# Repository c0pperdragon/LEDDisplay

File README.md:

# LEDDisplay

To go with all my lumacode digitizer boards, we also need something to 
display the output in a proper retro fashion. So a big LED matrix display that can accept
lumacode natively would be just the right thing for that.

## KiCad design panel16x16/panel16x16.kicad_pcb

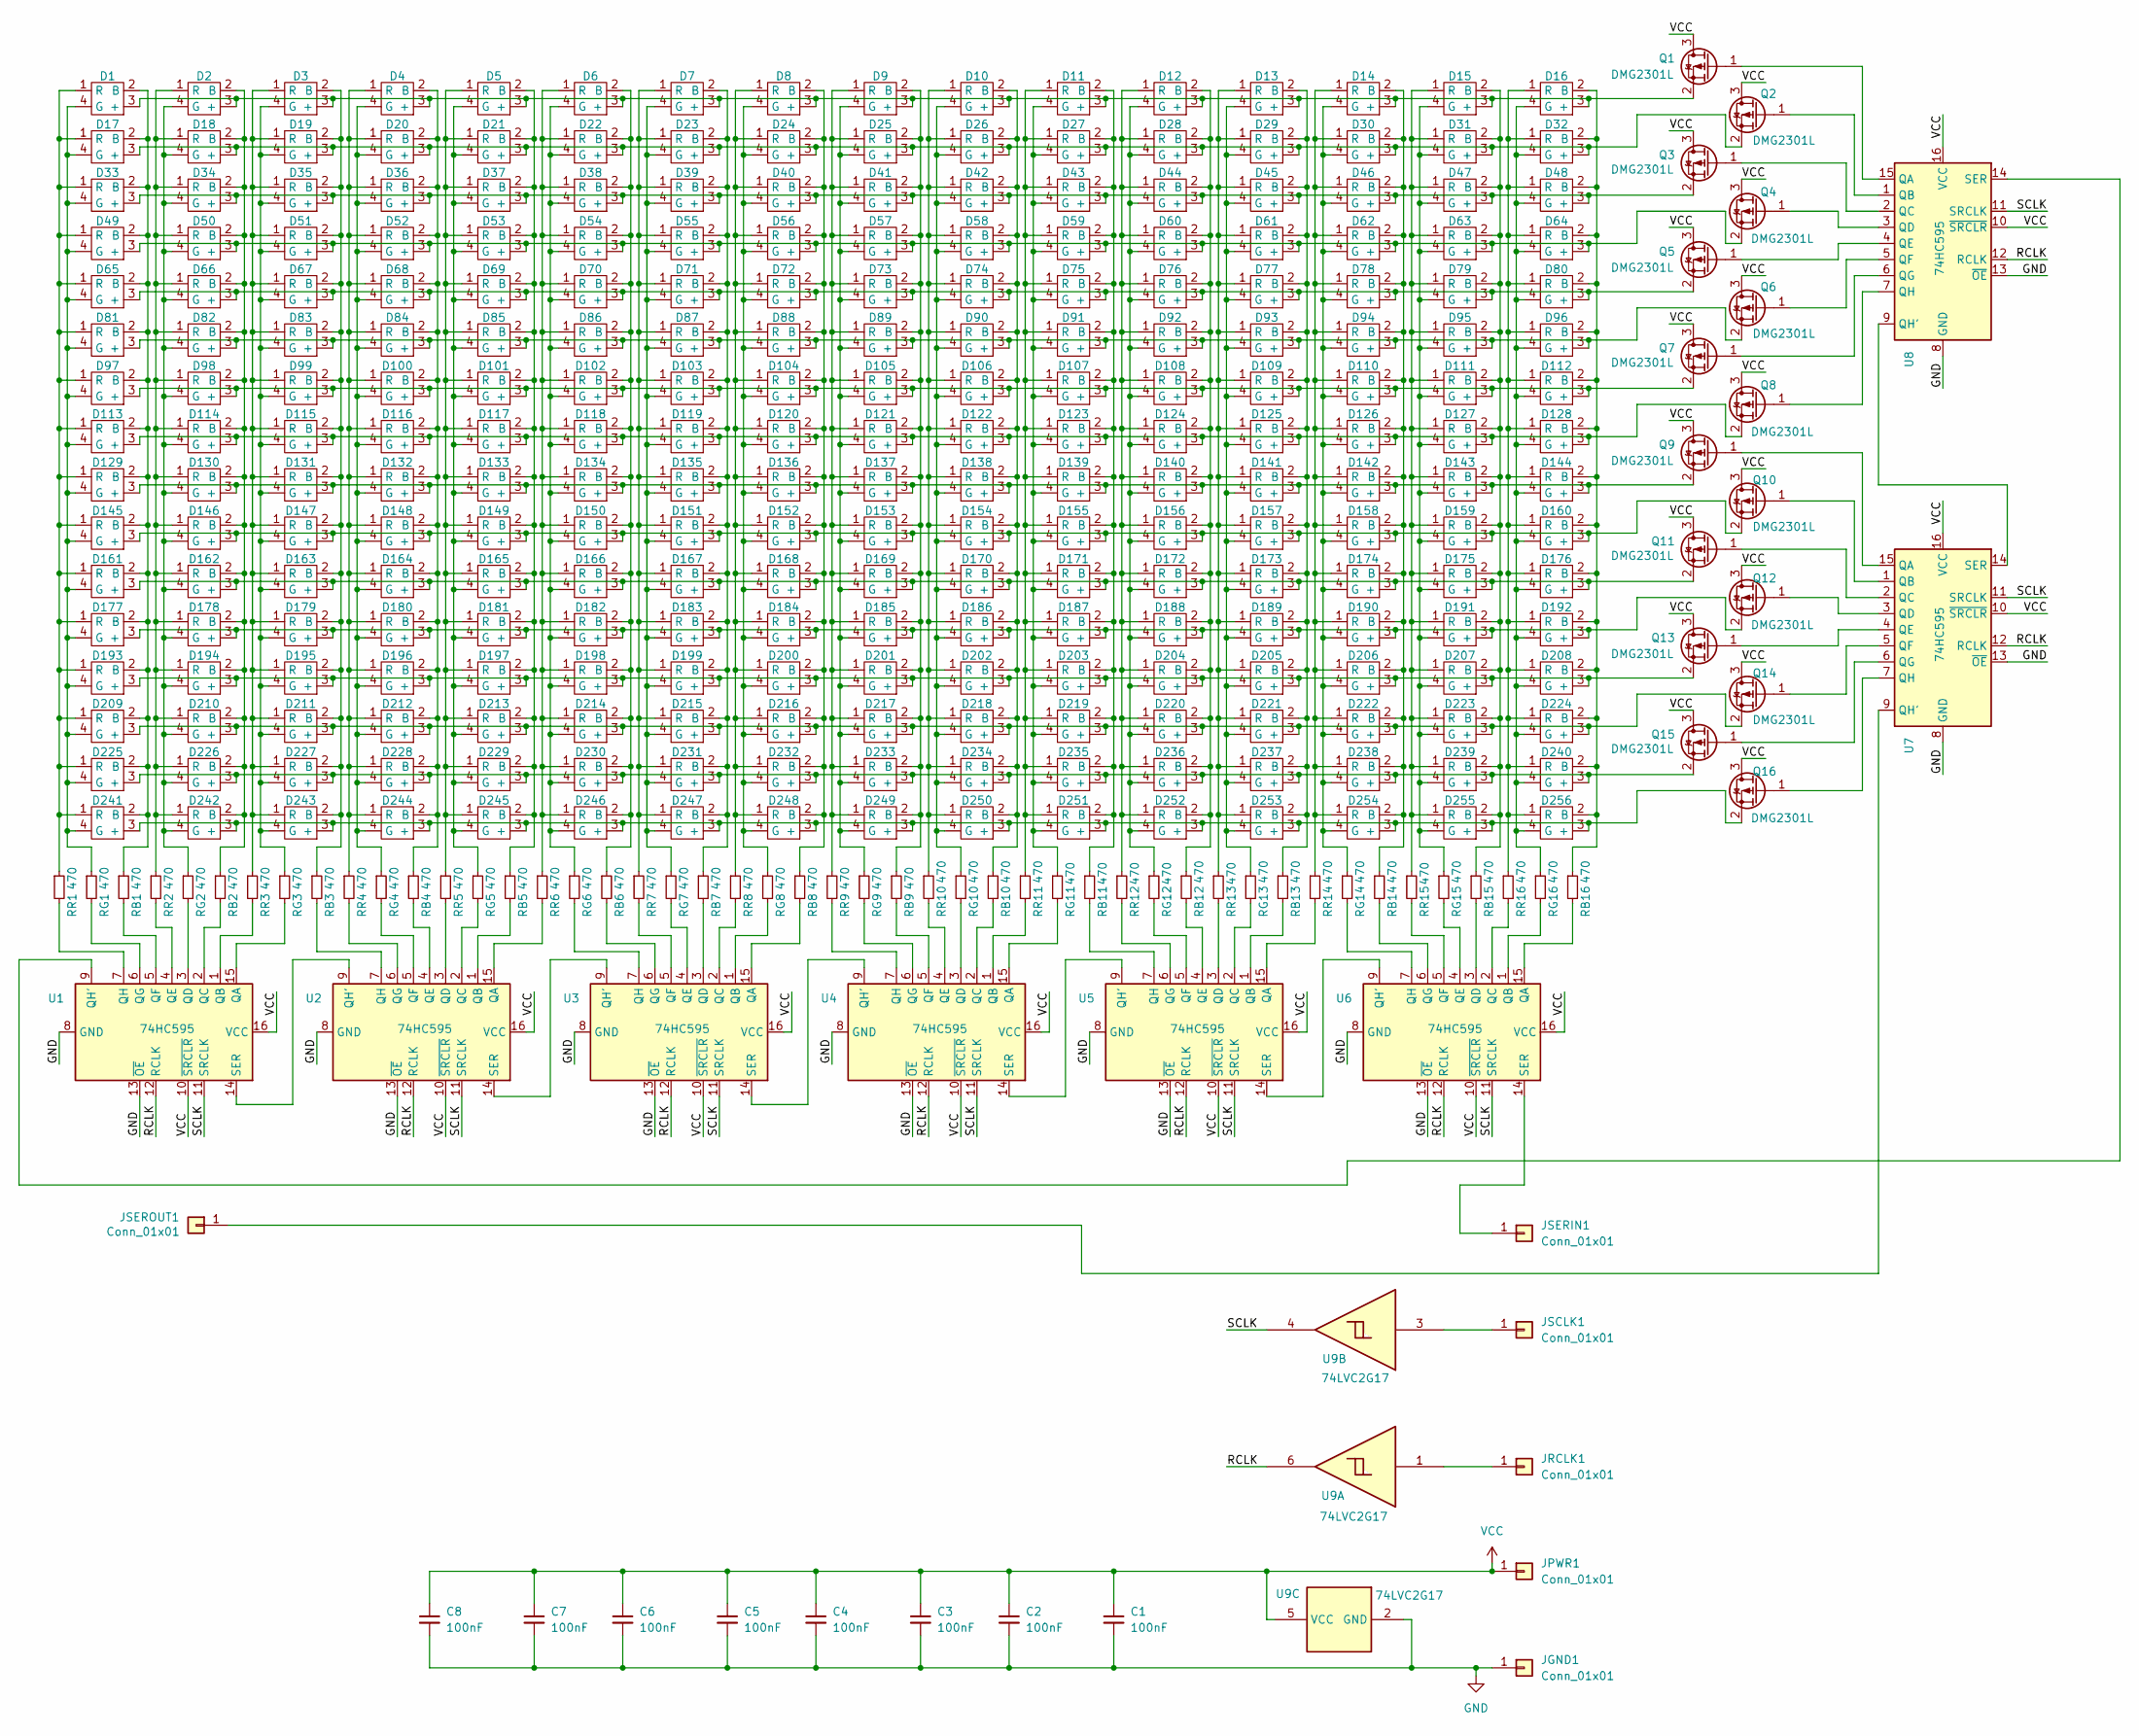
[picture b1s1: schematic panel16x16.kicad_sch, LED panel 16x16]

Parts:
C1, C2, C3, C4, C5, C6, C7, C8: 100nF; C_0603_1608Metric
D1, D2, D3, D4, D5, D6, D7, D8, D9, D10, D11, D12, D13, D14, D15, D16, D17, D18, D19, D20, D21, D22, D23, D24, D25, D26, D27, D28, D29, D30, D31, D32, D33, D34, D35, D36, D37, D38, D39, D40, D41, D42, D43, D44, D45, D46, D47, D48, D49, D50, D51, D52, D53, D54, D55, D56, D57, D58, D59, D60, D61, D62, D63, D64, D65, D66, D67, D68, D69, D70, D71, D72, D73, D74, D75, D76, D77, D78, D79, D80, D81, D82, D83, D84, D85, D86, D87, D88, D89, D90, D91, D92, D93, D94, D95, D96, D97, D98, D99, D100, D101, D102, D103, D104, D105, D106, D107, D108, D109, D110, D111, D112, D113, D114, D115, D116, D117, D118, D119, D120, D121, D122, D123, D124, D125, D126, D127, D128, D129, D130, D131, D132, D133, D134, D135, D136, D137, D138, D139, D140, D141, D142, D143, D144, D145, D146, D147, D148, D149, D150, D151, D152, D153, D154, D155, D156, D157, D158, D159, D160, D161, D162, D163, D164, D165, D166, D167, D168, D169, D170, D171, D172, D173, D174, D175, D176, D177, D178, D179, D180, D181, D182, D183, D184, D185, D186, D187, D188, D189, D190, D191, D192, D193, D194, D195, D196, D197, D198, D199, D200, D201, D202, D203, D204, D205, D206, D207, D208, D209, D210, D211, D212, D213, D214, D215, D216, D217, D218, D219, D220, D221, D222, D223, D224, D225, D226, D227, D228, D229, D230, D231, D232, D233, D234, D235, D236, D237, D238, D239, D240, D241, D242, D243, D244, D245, D246, D247, D248, D249, D250, D251, D252, D253, D254, D255, D256: B2020-RGBA
JGND1: Conn_01x01; TestPoint_Pad_2.0x2.0mm
JPWR1: Conn_01x01; TestPoint_Pad_2.0x2.0mm
JRCLK1: Conn_01x01; TestPoint_Pad_2.0x2.0mm
JSCLK1: Conn_01x01; TestPoint_Pad_2.0x2.0mm
JSERIN1: Conn_01x01; TestPoint_Pad_2.0x2.0mm
JSEROUT1: Conn_01x01; TestPoint_Pad_2.0x2.0mm
Q1, Q2, Q3, Q4, Q5, Q6, Q7, Q8, Q9, Q10, Q11, Q12, Q13, Q14, Q15, Q16: DMG2301L; SOT-23
RB1, RB2, RB3, RB4, RB5, RB6, RB7, RB8, RB9, RB10, RB11, RB12, RB13, RB14, RB15, RB16: 470; R_0603_1608Metric
RG1, RG2, RG3, RG4, RG5, RG6, RG7, RG8, RG9, RG10, RG11, RG12, RG13, RG14, RG15, RG16: 470; R_0603_1608Metric
RR1, RR2, RR3, RR4, RR5, RR6, RR7, RR8, RR9, RR10, RR11, RR12, RR13, RR14, RR15, RR16: 470; R_0603_1608Metric
U1, U2, U3, U4, U5, U6, U7, U8: 74HC595; TSSOP-16_4.4x5mm_P0.65mm
U9: 74LVC2G17; SOT-23-6

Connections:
/RCLK: U1.12 (RCLK), U2.12 (RCLK), U3.12 (RCLK), U4.12 (RCLK), U5.12 (RCLK), U6.12 (RCLK), U7.12 (RCLK), U8.12 (RCLK), U9.6
/SCLK: U1.11 (SRCLK), U2.11 (SRCLK), U3.11 (SRCLK), U4.11 (SRCLK), U5.11 (SRCLK), U6.11 (SRCLK), U7.11 (SRCLK), U8.11 (SRCLK), U9.4
GND: C1.2, C2.2, C3.2, C4.2, C5.2, C6.2, C7.2, C8.2, JGND1.1, U1.8 (GND), U1.13 (~OE), U2.8 (GND), U2.13 (~OE), U3.8 (GND), U3.13 (~OE), U4.8 (GND), U4.13 (~OE), U5.8 (GND), U5.13 (~OE), U6.8 (GND), U6.13 (~OE), U7.8 (GND), U7.13 (~OE), U8.8 (GND), U8.13 (~OE), U9.2 (GND)
unnamed: D1.3 (+), D2.3 (+), D3.3 (+), D4.3 (+), D5.3 (+), D6.3 (+), D7.3 (+), D8.3 (+), D9.3 (+), D10.3 (+), D11.3 (+), D12.3 (+), D13.3 (+), D14.3 (+), D15.3 (+), D16.3 (+), Q1.2 (S)
unnamed: D1.2 (B), D17.2 (B), D33.2 (B), D49.2 (B), D65.2 (B), D81.2 (B), D97.2 (B), D113.2 (B), D129.2 (B), D145.2 (B), D161.2 (B), D177.2 (B), D193.2 (B), D209.2 (B), D225.2 (B), D241.2 (B), RB1.1
unnamed: D1.4 (G), D17.4 (G), D33.4 (G), D49.4 (G), D65.4 (G), D81.4 (G), D97.4 (G), D113.4 (G), D129.4 (G), D145.4 (G), D161.4 (G), D177.4 (G), D193.4 (G), D209.4 (G), D225.4 (G), D241.4 (G), RG1.1
unnamed: D1.1 (R), D17.1 (R), D33.1 (R), D49.1 (R), D65.1 (R), D81.1 (R), D97.1 (R), D113.1 (R), D129.1 (R), D145.1 (R), D161.1 (R), D177.1 (R), D193.1 (R), D209.1 (R), D225.1 (R), D241.1 (R), RR1.1
unnamed: D10.2 (B), D26.2 (B), D42.2 (B), D58.2 (B), D74.2 (B), D90.2 (B), D106.2 (B), D122.2 (B), D138.2 (B), D154.2 (B), D170.2 (B), D186.2 (B), D202.2 (B), D218.2 (B), D234.2 (B), D250.2 (B), RB10.1
unnamed: D10.4 (G), D26.4 (G), D42.4 (G), D58.4 (G), D74.4 (G), D90.4 (G), D106.4 (G), D122.4 (G), D138.4 (G), D154.4 (G), D170.4 (G), D186.4 (G), D202.4 (G), D218.4 (G), D234.4 (G), D250.4 (G), RG10.1
unnamed: D10.1 (R), D26.1 (R), D42.1 (R), D58.1 (R), D74.1 (R), D90.1 (R), D106.1 (R), D122.1 (R), D138.1 (R), D154.1 (R), D170.1 (R), D186.1 (R), D202.1 (R), D218.1 (R), D234.1 (R), D250.1 (R), RR10.1
unnamed: D17.3 (+), D18.3 (+), D19.3 (+), D20.3 (+), D21.3 (+), D22.3 (+), D23.3 (+), D24.3 (+), D25.3 (+), D26.3 (+), D27.3 (+), D28.3 (+), D29.3 (+), D30.3 (+), D31.3 (+), D32.3 (+), Q2.2 (S)
unnamed: D33.3 (+), D34.3 (+), D35.3 (+), D36.3 (+), D37.3 (+), D38.3 (+), D39.3 (+), D40.3 (+), D41.3 (+), D42.3 (+), D43.3 (+), D44.3 (+), D45.3 (+), D46.3 (+), D47.3 (+), D48.3 (+), Q3.2 (S)
unnamed: D49.3 (+), D50.3 (+), D51.3 (+), D52.3 (+), D53.3 (+), D54.3 (+), D55.3 (+), D56.3 (+), D57.3 (+), D58.3 (+), D59.3 (+), D60.3 (+), D61.3 (+), D62.3 (+), D63.3 (+), D64.3 (+), Q4.2 (S)
unnamed: D65.3 (+), D66.3 (+), D67.3 (+), D68.3 (+), D69.3 (+), D70.3 (+), D71.3 (+), D72.3 (+), D73.3 (+), D74.3 (+), D75.3 (+), D76.3 (+), D77.3 (+), D78.3 (+), D79.3 (+), D80.3 (+), Q5.2 (S)
unnamed: D81.3 (+), D82.3 (+), D83.3 (+), D84.3 (+), D85.3 (+), D86.3 (+), D87.3 (+), D88.3 (+), D89.3 (+), D90.3 (+), D91.3 (+), D92.3 (+), D93.3 (+), D94.3 (+), D95.3 (+), D96.3 (+), Q6.2 (S)
unnamed: D97.3 (+), D98.3 (+), D99.3 (+), D100.3 (+), D101.3 (+), D102.3 (+), D103.3 (+), D104.3 (+), D105.3 (+), D106.3 (+), D107.3 (+), D108.3 (+), D109.3 (+), D110.3 (+), D111.3 (+), D112.3 (+), Q7.2 (S)
unnamed: D4.2 (B), D20.2 (B), D36.2 (B), D52.2 (B), D68.2 (B), D84.2 (B), D100.2 (B), D116.2 (B), D132.2 (B), D148.2 (B), D164.2 (B), D180.2 (B), D196.2 (B), D212.2 (B), D228.2 (B), D244.2 (B), RB4.1
unnamed: D4.4 (G), D20.4 (G), D36.4 (G), D52.4 (G), D68.4 (G), D84.4 (G), D100.4 (G), D116.4 (G), D132.4 (G), D148.4 (G), D164.4 (G), D180.4 (G), D196.4 (G), D212.4 (G), D228.4 (G), D244.4 (G), RG4.1
unnamed: D4.1 (R), D20.1 (R), D36.1 (R), D52.1 (R), D68.1 (R), D84.1 (R), D100.1 (R), D116.1 (R), D132.1 (R), D148.1 (R), D164.1 (R), D180.1 (R), D196.1 (R), D212.1 (R), D228.1 (R), D244.1 (R), RR4.1
unnamed: D5.2 (B), D21.2 (B), D37.2 (B), D53.2 (B), D69.2 (B), D85.2 (B), D101.2 (B), D117.2 (B), D133.2 (B), D149.2 (B), D165.2 (B), D181.2 (B), D197.2 (B), D213.2 (B), D229.2 (B), D245.2 (B), RB5.1
unnamed: D5.4 (G), D21.4 (G), D37.4 (G), D53.4 (G), D69.4 (G), D85.4 (G), D101.4 (G), D117.4 (G), D133.4 (G), D149.4 (G), D165.4 (G), D181.4 (G), D197.4 (G), D213.4 (G), D229.4 (G), D245.4 (G), RG5.1
unnamed: D5.1 (R), D21.1 (R), D37.1 (R), D53.1 (R), D69.1 (R), D85.1 (R), D101.1 (R), D117.1 (R), D133.1 (R), D149.1 (R), D165.1 (R), D181.1 (R), D197.1 (R), D213.1 (R), D229.1 (R), D245.1 (R), RR5.1
unnamed: D6.2 (B), D22.2 (B), D38.2 (B), D54.2 (B), D70.2 (B), D86.2 (B), D102.2 (B), D118.2 (B), D134.2 (B), D150.2 (B), D166.2 (B), D182.2 (B), D198.2 (B), D214.2 (B), D230.2 (B), D246.2 (B), RB6.1
unnamed: D6.4 (G), D22.4 (G), D38.4 (G), D54.4 (G), D70.4 (G), D86.4 (G), D102.4 (G), D118.4 (G), D134.4 (G), D150.4 (G), D166.4 (G), D182.4 (G), D198.4 (G), D214.4 (G), D230.4 (G), D246.4 (G), RG6.1
unnamed: D6.1 (R), D22.1 (R), D38.1 (R), D54.1 (R), D70.1 (R), D86.1 (R), D102.1 (R), D118.1 (R), D134.1 (R), D150.1 (R), D166.1 (R), D182.1 (R), D198.1 (R), D214.1 (R), D230.1 (R), D246.1 (R), RR6.1
unnamed: D7.2 (B), D23.2 (B), D39.2 (B), D55.2 (B), D71.2 (B), D87.2 (B), D103.2 (B), D119.2 (B), D135.2 (B), D151.2 (B), D167.2 (B), D183.2 (B), D199.2 (B), D215.2 (B), D231.2 (B), D247.2 (B), RB7.1
unnamed: D7.4 (G), D23.4 (G), D39.4 (G), D55.4 (G), D71.4 (G), D87.4 (G), D103.4 (G), D119.4 (G), D135.4 (G), D151.4 (G), D167.4 (G), D183.4 (G), D199.4 (G), D215.4 (G), D231.4 (G), D247.4 (G), RG7.1
unnamed: D7.1 (R), D23.1 (R), D39.1 (R), D55.1 (R), D71.1 (R), D87.1 (R), D103.1 (R), D119.1 (R), D135.1 (R), D151.1 (R), D167.1 (R), D183.1 (R), D199.1 (R), D215.1 (R), D231.1 (R), D247.1 (R), RR7.1
unnamed: D8.2 (B), D24.2 (B), D40.2 (B), D56.2 (B), D72.2 (B), D88.2 (B), D104.2 (B), D120.2 (B), D136.2 (B), D152.2 (B), D168.2 (B), D184.2 (B), D200.2 (B), D216.2 (B), D232.2 (B), D248.2 (B), RB8.1
unnamed: D8.4 (G), D24.4 (G), D40.4 (G), D56.4 (G), D72.4 (G), D88.4 (G), D104.4 (G), D120.4 (G), D136.4 (G), D152.4 (G), D168.4 (G), D184.4 (G), D200.4 (G), D216.4 (G), D232.4 (G), D248.4 (G), RG8.1
unnamed: D8.1 (R), D24.1 (R), D40.1 (R), D56.1 (R), D72.1 (R), D88.1 (R), D104.1 (R), D120.1 (R), D136.1 (R), D152.1 (R), D168.1 (R), D184.1 (R), D200.1 (R), D216.1 (R), D232.1 (R), D248.1 (R), RR8.1
unnamed: D9.2 (B), D25.2 (B), D41.2 (B), D57.2 (B), D73.2 (B), D89.2 (B), D105.2 (B), D121.2 (B), D137.2 (B), D153.2 (B), D169.2 (B), D185.2 (B), D201.2 (B), D217.2 (B), D233.2 (B), D249.2 (B), RB9.1
unnamed: D9.4 (G), D25.4 (G), D41.4 (G), D57.4 (G), D73.4 (G), D89.4 (G), D105.4 (G), D121.4 (G), D137.4 (G), D153.4 (G), D169.4 (G), D185.4 (G), D201.4 (G), D217.4 (G), D233.4 (G), D249.4 (G), RG9.1
unnamed: D9.1 (R), D25.1 (R), D41.1 (R), D57.1 (R), D73.1 (R), D89.1 (R), D105.1 (R), D121.1 (R), D137.1 (R), D153.1 (R), D169.1 (R), D185.1 (R), D201.1 (R), D217.1 (R), D233.1 (R), D249.1 (R), RR9.1
unnamed: D11.2 (B), D27.2 (B), D43.2 (B), D59.2 (B), D75.2 (B), D91.2 (B), D107.2 (B), D123.2 (B), D139.2 (B), D155.2 (B), D171.2 (B), D187.2 (B), D203.2 (B), D219.2 (B), D235.2 (B), D251.2 (B), RB11.1
unnamed: D11.4 (G), D27.4 (G), D43.4 (G), D59.4 (G), D75.4 (G), D91.4 (G), D107.4 (G), D123.4 (G), D139.4 (G), D155.4 (G), D171.4 (G), D187.4 (G), D203.4 (G), D219.4 (G), D235.4 (G), D251.4 (G), RG11.1
unnamed: D11.1 (R), D27.1 (R), D43.1 (R), D59.1 (R), D75.1 (R), D91.1 (R), D107.1 (R), D123.1 (R), D139.1 (R), D155.1 (R), D171.1 (R), D187.1 (R), D203.1 (R), D219.1 (R), D235.1 (R), D251.1 (R), RR11.1
unnamed: D12.2 (B), D28.2 (B), D44.2 (B), D60.2 (B), D76.2 (B), D92.2 (B), D108.2 (B), D124.2 (B), D140.2 (B), D156.2 (B), D172.2 (B), D188.2 (B), D204.2 (B), D220.2 (B), D236.2 (B), D252.2 (B), RB12.1
unnamed: D12.4 (G), D28.4 (G), D44.4 (G), D60.4 (G), D76.4 (G), D92.4 (G), D108.4 (G), D124.4 (G), D140.4 (G), D156.4 (G), D172.4 (G), D188.4 (G), D204.4 (G), D220.4 (G), D236.4 (G), D252.4 (G), RG12.1
unnamed: D12.1 (R), D28.1 (R), D44.1 (R), D60.1 (R), D76.1 (R), D92.1 (R), D108.1 (R), D124.1 (R), D140.1 (R), D156.1 (R), D172.1 (R), D188.1 (R), D204.1 (R), D220.1 (R), D236.1 (R), D252.1 (R), RR12.1
unnamed: D13.2 (B), D29.2 (B), D45.2 (B), D61.2 (B), D77.2 (B), D93.2 (B), D109.2 (B), D125.2 (B), D141.2 (B), D157.2 (B), D173.2 (B), D189.2 (B), D205.2 (B), D221.2 (B), D237.2 (B), D253.2 (B), RB13.1
unnamed: D13.4 (G), D29.4 (G), D45.4 (G), D61.4 (G), D77.4 (G), D93.4 (G), D109.4 (G), D125.4 (G), D141.4 (G), D157.4 (G), D173.4 (G), D189.4 (G), D205.4 (G), D221.4 (G), D237.4 (G), D253.4 (G), RG13.1
unnamed: D13.1 (R), D29.1 (R), D45.1 (R), D61.1 (R), D77.1 (R), D93.1 (R), D109.1 (R), D125.1 (R), D141.1 (R), D157.1 (R), D173.1 (R), D189.1 (R), D205.1 (R), D221.1 (R), D237.1 (R), D253.1 (R), RR13.1
unnamed: D14.2 (B), D30.2 (B), D46.2 (B), D62.2 (B), D78.2 (B), D94.2 (B), D110.2 (B), D126.2 (B), D142.2 (B), D158.2 (B), D174.2 (B), D190.2 (B), D206.2 (B), D222.2 (B), D238.2 (B), D254.2 (B), RB14.1
unnamed: D14.4 (G), D30.4 (G), D46.4 (G), D62.4 (G), D78.4 (G), D94.4 (G), D110.4 (G), D126.4 (G), D142.4 (G), D158.4 (G), D174.4 (G), D190.4 (G), D206.4 (G), D222.4 (G), D238.4 (G), D254.4 (G), RG14.1
unnamed: D14.1 (R), D30.1 (R), D46.1 (R), D62.1 (R), D78.1 (R), D94.1 (R), D110.1 (R), D126.1 (R), D142.1 (R), D158.1 (R), D174.1 (R), D190.1 (R), D206.1 (R), D222.1 (R), D238.1 (R), D254.1 (R), RR14.1
unnamed: D15.2 (B), D31.2 (B), D47.2 (B), D63.2 (B), D79.2 (B), D95.2 (B), D111.2 (B), D127.2 (B), D143.2 (B), D159.2 (B), D175.2 (B), D191.2 (B), D207.2 (B), D223.2 (B), D239.2 (B), D255.2 (B), RB15.1
unnamed: D15.4 (G), D31.4 (G), D47.4 (G), D63.4 (G), D79.4 (G), D95.4 (G), D111.4 (G), D127.4 (G), D143.4 (G), D159.4 (G), D175.4 (G), D191.4 (G), D207.4 (G), D223.4 (G), D239.4 (G), D255.4 (G), RG15.1
unnamed: D15.1 (R), D31.1 (R), D47.1 (R), D63.1 (R), D79.1 (R), D95.1 (R), D111.1 (R), D127.1 (R), D143.1 (R), D159.1 (R), D175.1 (R), D191.1 (R), D207.1 (R), D223.1 (R), D239.1 (R), D255.1 (R), RR15.1
unnamed: D16.2 (B), D32.2 (B), D48.2 (B), D64.2 (B), D80.2 (B), D96.2 (B), D112.2 (B), D128.2 (B), D144.2 (B), D160.2 (B), D176.2 (B), D192.2 (B), D208.2 (B), D224.2 (B), D240.2 (B), D256.2 (B), RB16.1
unnamed: D16.4 (G), D32.4 (G), D48.4 (G), D64.4 (G), D80.4 (G), D96.4 (G), D112.4 (G), D128.4 (G), D144.4 (G), D160.4 (G), D176.4 (G), D192.4 (G), D208.4 (G), D224.4 (G), D240.4 (G), D256.4 (G), RG16.1
unnamed: D16.1 (R), D32.1 (R), D48.1 (R), D64.1 (R), D80.1 (R), D96.1 (R), D112.1 (R), D128.1 (R), D144.1 (R), D160.1 (R), D176.1 (R), D192.1 (R), D208.1 (R), D224.1 (R), D240.1 (R), D256.1 (R), RR16.1
unnamed: D113.3 (+), D114.3 (+), D115.3 (+), D116.3 (+), D117.3 (+), D118.3 (+), D119.3 (+), D120.3 (+), D121.3 (+), D122.3 (+), D123.3 (+), D124.3 (+), D125.3 (+), D126.3 (+), D127.3 (+), D128.3 (+), Q8.2 (S)
unnamed: D2.2 (B), D18.2 (B), D34.2 (B), D50.2 (B), D66.2 (B), D82.2 (B), D98.2 (B), D114.2 (B), D130.2 (B), D146.2 (B), D162.2 (B), D178.2 (B), D194.2 (B), D210.2 (B), D226.2 (B), D242.2 (B), RB2.1
unnamed: D2.4 (G), D18.4 (G), D34.4 (G), D50.4 (G), D66.4 (G), D82.4 (G), D98.4 (G), D114.4 (G), D130.4 (G), D146.4 (G), D162.4 (G), D178.4 (G), D194.4 (G), D210.4 (G), D226.4 (G), D242.4 (G), RG2.1
unnamed: D2.1 (R), D18.1 (R), D34.1 (R), D50.1 (R), D66.1 (R), D82.1 (R), D98.1 (R), D114.1 (R), D130.1 (R), D146.1 (R), D162.1 (R), D178.1 (R), D194.1 (R), D210.1 (R), D226.1 (R), D242.1 (R), RR2.1
unnamed: D3.2 (B), D19.2 (B), D35.2 (B), D51.2 (B), D67.2 (B), D83.2 (B), D99.2 (B), D115.2 (B), D131.2 (B), D147.2 (B), D163.2 (B), D179.2 (B), D195.2 (B), D211.2 (B), D227.2 (B), D243.2 (B), RB3.1
unnamed: D3.4 (G), D19.4 (G), D35.4 (G), D51.4 (G), D67.4 (G), D83.4 (G), D99.4 (G), D115.4 (G), D131.4 (G), D147.4 (G), D163.4 (G), D179.4 (G), D195.4 (G), D211.4 (G), D227.4 (G), D243.4 (G), RG3.1
unnamed: D3.1 (R), D19.1 (R), D35.1 (R), D51.1 (R), D67.1 (R), D83.1 (R), D99.1 (R), D115.1 (R), D131.1 (R), D147.1 (R), D163.1 (R), D179.1 (R), D195.1 (R), D211.1 (R), D227.1 (R), D243.1 (R), RR3.1
unnamed: D129.3 (+), D130.3 (+), D131.3 (+), D132.3 (+), D133.3 (+), D134.3 (+), D135.3 (+), D136.3 (+), D137.3 (+), D138.3 (+), D139.3 (+), D140.3 (+), D141.3 (+), D142.3 (+), D143.3 (+), D144.3 (+), Q9.2 (S)
unnamed: D145.3 (+), D146.3 (+), D147.3 (+), D148.3 (+), D149.3 (+), D150.3 (+), D151.3 (+), D152.3 (+), D153.3 (+), D154.3 (+), D155.3 (+), D156.3 (+), D157.3 (+), D158.3 (+), D159.3 (+), D160.3 (+), Q10.2 (S)
unnamed: D161.3 (+), D162.3 (+), D163.3 (+), D164.3 (+), D165.3 (+), D166.3 (+), D167.3 (+), D168.3 (+), D169.3 (+), D170.3 (+), D171.3 (+), D172.3 (+), D173.3 (+), D174.3 (+), D175.3 (+), D176.3 (+), Q11.2 (S)
unnamed: D177.3 (+), D178.3 (+), D179.3 (+), D180.3 (+), D181.3 (+), D182.3 (+), D183.3 (+), D184.3 (+), D185.3 (+), D186.3 (+), D187.3 (+), D188.3 (+), D189.3 (+), D190.3 (+), D191.3 (+), D192.3 (+), Q12.2 (S)
unnamed: D193.3 (+), D194.3 (+), D195.3 (+), D196.3 (+), D197.3 (+), D198.3 (+), D199.3 (+), D200.3 (+), D201.3 (+), D202.3 (+), D203.3 (+), D204.3 (+), D205.3 (+), D206.3 (+), D207.3 (+), D208.3 (+), Q13.2 (S)
unnamed: D209.3 (+), D210.3 (+), D211.3 (+), D212.3 (+), D213.3 (+), D214.3 (+), D215.3 (+), D216.3 (+), D217.3 (+), D218.3 (+), D219.3 (+), D220.3 (+), D221.3 (+), D222.3 (+), D223.3 (+), D224.3 (+), Q14.2 (S)
unnamed: D225.3 (+), D226.3 (+), D227.3 (+), D228.3 (+), D229.3 (+), D230.3 (+), D231.3 (+), D232.3 (+), D233.3 (+), D234.3 (+), D235.3 (+), D236.3 (+), D237.3 (+), D238.3 (+), D239.3 (+), D240.3 (+), Q15.2 (S)
unnamed: D241.3 (+), D242.3 (+), D243.3 (+), D244.3 (+), D245.3 (+), D246.3 (+), D247.3 (+), D248.3 (+), D249.3 (+), D250.3 (+), D251.3 (+), D252.3 (+), D253.3 (+), D254.3 (+), D255.3 (+), D256.3 (+), Q16.2 (S)
unnamed: JRCLK1.1, U9.1
unnamed: JSCLK1.1, U9.3
unnamed: JSERIN1.1, U6.14 (SER)
unnamed: JSEROUT1.1, U7.9 (QH')
unnamed: Q1.1 (G), U8.15 (QA)
unnamed: Q2.1 (G), U8.1 (QB)
unnamed: Q3.1 (G), U8.2 (QC)
unnamed: Q4.1 (G), U8.3 (QD)
unnamed: Q5.1 (G), U8.4 (QE)
unnamed: Q6.1 (G), U8.5 (QF)
unnamed: Q7.1 (G), U8.6 (QG)
unnamed: Q8.1 (G), U8.7 (QH)
unnamed: Q9.1 (G), U7.15 (QA)
unnamed: Q10.1 (G), U7.1 (QB)
unnamed: Q11.1 (G), U7.2 (QC)
unnamed: Q12.1 (G), U7.3 (QD)
unnamed: Q13.1 (G), U7.4 (QE)
unnamed: Q14.1 (G), U7.5 (QF)
unnamed: Q15.1 (G), U7.6 (QG)
unnamed: Q16.1 (G), U7.7 (QH)
unnamed: RG3.2, U1.15 (QA)
unnamed: RR3.2, U1.1 (QB)
unnamed: RB2.2, U1.2 (QC)
unnamed: RG2.2, U1.3 (QD)
unnamed: RR2.2, U1.4 (QE)
unnamed: RB1.2, U1.5 (QF)
unnamed: RG1.2, U1.6 (QG)
unnamed: U1.9 (QH'), U8.14 (SER)
unnamed: RR1.2, U1.7 (QH)
unnamed: U1.14 (SER), U2.9 (QH')
unnamed: RR6.2, U2.15 (QA)
unnamed: RB5.2, U2.1 (QB)
unnamed: RG5.2, U2.2 (QC)
unnamed: RR5.2, U2.3 (QD)
unnamed: RB4.2, U2.4 (QE)
unnamed: RG4.2, U2.5 (QF)
unnamed: RR4.2, U2.6 (QG)
unnamed: RB3.2, U2.7 (QH)
unnamed: U2.14 (SER), U3.9 (QH')
unnamed: RB8.2, U3.15 (QA)
unnamed: RG8.2, U3.1 (QB)
unnamed: RR8.2, U3.2 (QC)
unnamed: RB7.2, U3.3 (QD)
unnamed: RG7.2, U3.4 (QE)
unnamed: RR7.2, U3.5 (QF)
unnamed: RB6.2, U3.6 (QG)
unnamed: RG6.2, U3.7 (QH)
unnamed: U3.14 (SER), U4.9 (QH')
unnamed: RG11.2, U4.15 (QA)
unnamed: RR11.2, U4.1 (QB)
unnamed: RB10.2, U4.2 (QC)
unnamed: RG10.2, U4.3 (QD)
unnamed: RR10.2, U4.4 (QE)
unnamed: RB9.2, U4.5 (QF)
unnamed: RG9.2, U4.6 (QG)
unnamed: RR9.2, U4.7 (QH)
unnamed: U4.14 (SER), U5.9 (QH')
unnamed: RR14.2, U5.15 (QA)
unnamed: RB13.2, U5.1 (QB)
unnamed: RG13.2, U5.2 (QC)
unnamed: RR13.2, U5.3 (QD)
unnamed: RB12.2, U5.4 (QE)
unnamed: RG12.2, U5.5 (QF)
unnamed: RR12.2, U5.6 (QG)
unnamed: RB11.2, U5.7 (QH)
unnamed: U5.14 (SER), U6.9 (QH')
unnamed: RB16.2, U6.15 (QA)
unnamed: RG16.2, U6.1 (QB)
unnamed: RR16.2, U6.2 (QC)
unnamed: RB15.2, U6.3 (QD)
unnamed: RG15.2, U6.4 (QE)
unnamed: RR15.2, U6.5 (QF)
unnamed: RB14.2, U6.6 (QG)
unnamed: RG14.2, U6.7 (QH)
unnamed: U7.14 (SER), U8.9 (QH')
VCC: C1.1, C2.1, C3.1, C4.1, C5.1, C6.1, C7.1, C8.1, JPWR1.1, Q1.3 (D), Q2.3 (D), Q3.3 (D), Q4.3 (D), Q5.3 (D), Q6.3 (D), Q7.3 (D), Q8.3 (D), Q9.3 (D), Q10.3 (D), Q11.3 (D), Q12.3 (D), Q13.3 (D), Q14.3 (D), Q15.3 (D), Q16.3 (D), U1.10 (~SRCLR), U1.16 (VCC), U2.10 (~SRCLR), U2.16 (VCC), U3.10 (~SRCLR), U3.16 (VCC), U4.10 (~SRCLR), U4.16 (VCC), U5.10 (~SRCLR), U5.16 (VCC), U6.10 (~SRCLR), U6.16 (VCC), U7.10 (~SRCLR), U7.16 (VCC), U8.10 (~SRCLR), U8.16 (VCC), U9.5 (VCC)

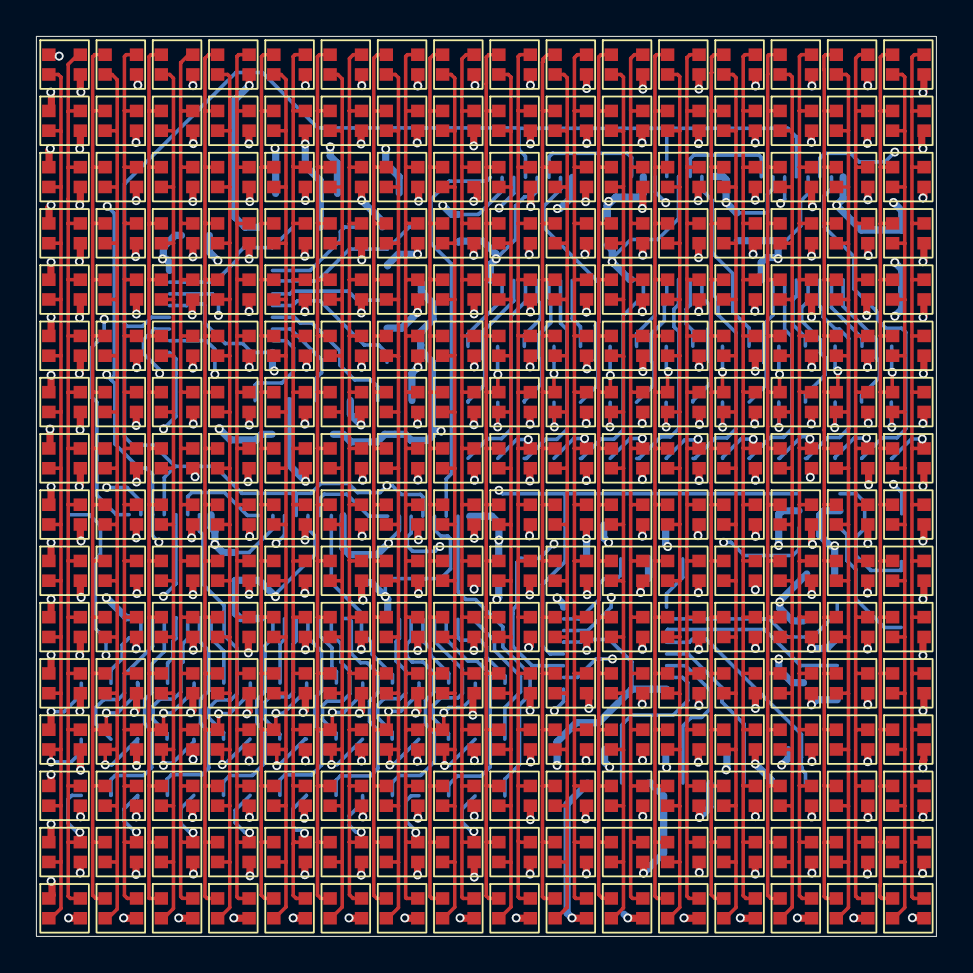
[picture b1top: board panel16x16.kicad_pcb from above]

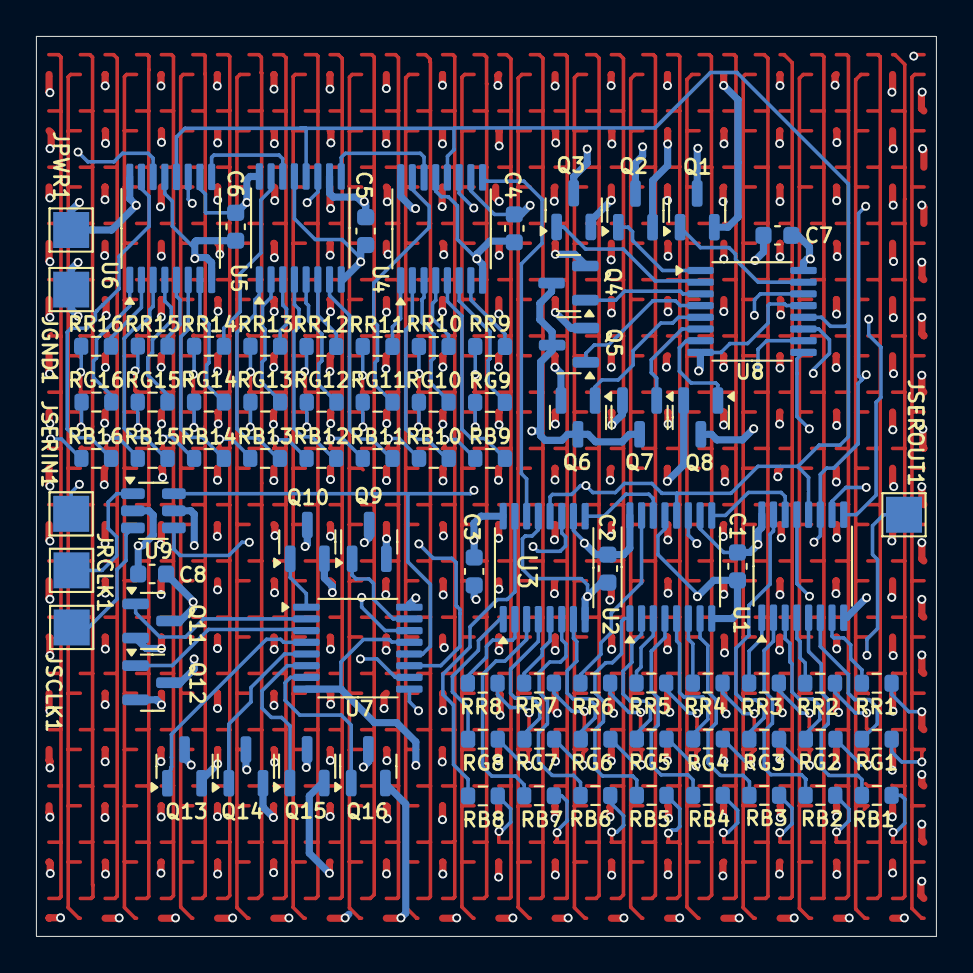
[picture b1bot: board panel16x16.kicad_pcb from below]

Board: 4 copper layers, 50.0 x 50.0 mm, 343 parts (87 on the bottom side), 143 nets.

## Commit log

2025-04-11 PCB design
2025-04-12 Finish PCB design
2025-07-30 Test with solid single color
2025-07-31 Modify control board to allow latching without progressing line
2025-09-30 Some test code
2025-10-10 Rewire GPIO for ease of programming
2025-10-14 Nearly working test picture
2025-10-16 Get a consistent image, even if the pixel clock is too slow now.
2025-10-17 Rework shifter to allow memory organization line by line
2025-10-18 Drive OE pin for exact amount of times using the PIO system. This leaves the CPU for other tasks.
2025-10-19 Use 200MHz system clock so CPU can convert incomming data lines in time.
2025-10-28 Pico receives pixel data from FPGA
2025-10-31 Tweak signal timings
2025-10-31 Fix least significant bit in data conversion
2025-10-31 Keep row latch correctly in sync with current line
2025-11-05 Change assignment for connector cable
2025-12-26 Show test image from Pi to test output circuitry and code
2025-12-26 More tweaking of output code
2025-12-27 More signal timing tweaks. Finally working.
2025-12-29 Wiring of HDMI connector
2025-12-30 Send EDID
2026-01-03 Get EDID transmission working
2026-01-05 Get HDMI decoding working
2026-01-07 Tweak number of total pixels for an even 256 lines output
2026-01-09 Rework FPGA to Pico interfacing
2026-01-09 Working Pico code for adjusted transfer protocol
2026-01-10 Working nicely now
2026-01-11 Finally, a working version
2026-01-31 Reduce brightnes
